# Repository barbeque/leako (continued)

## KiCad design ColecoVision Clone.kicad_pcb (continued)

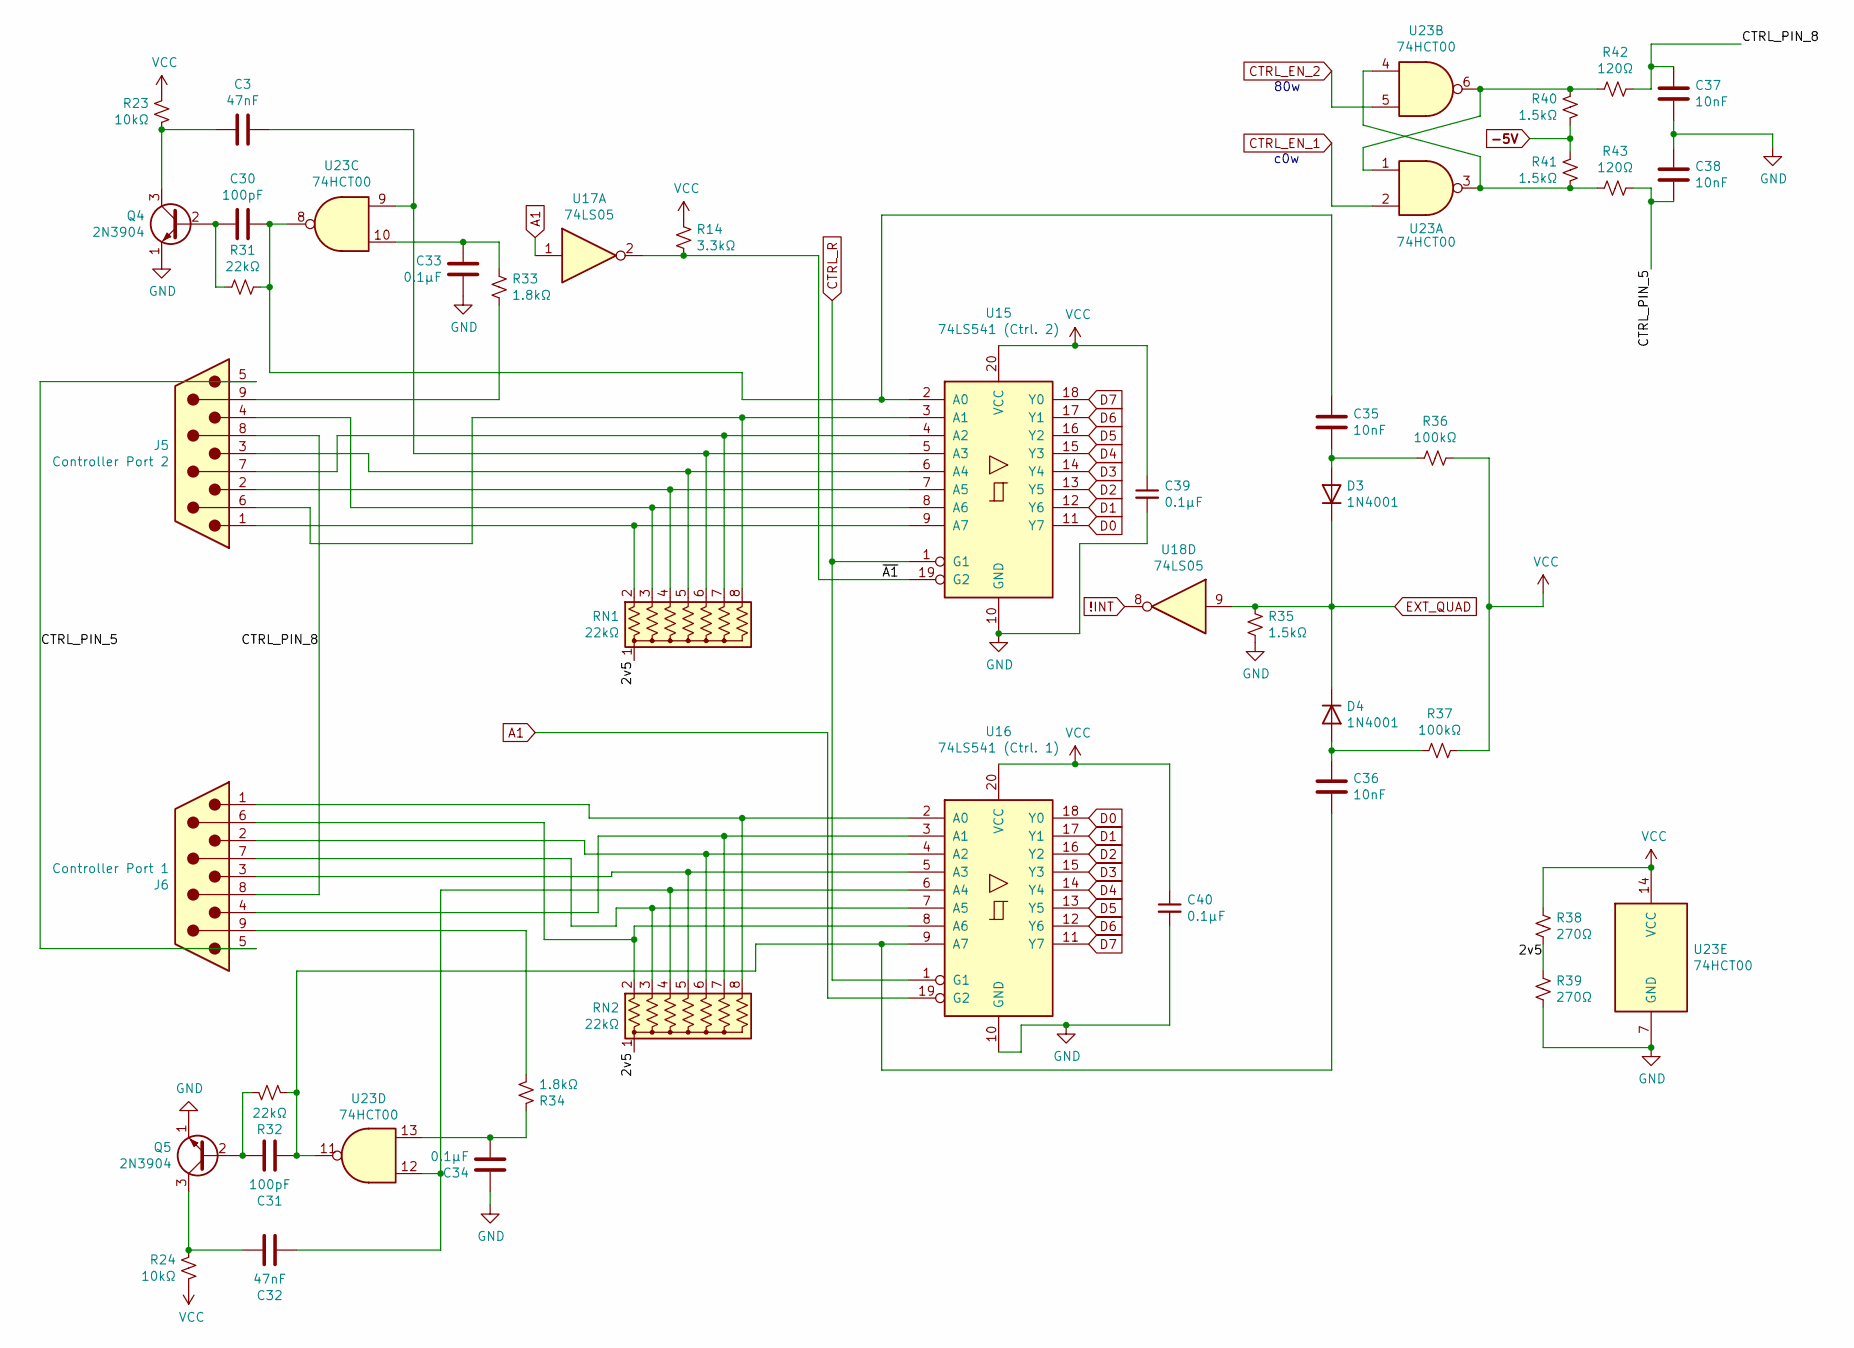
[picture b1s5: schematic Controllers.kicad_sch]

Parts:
C3, C32: 47nF; C_0805_HandSoldering; DigiKey 732-8059-1-ND
C30, C31: 100pF; C_0805_HandSoldering; DigiKey 732-12161-1-ND
C33, C34: 0.1µF; C_0805_HandSoldering; DigiKey 1276-1099-1-ND
C35, C36, C37, C38: 10nF; C_0805_HandSoldering; DigiKey 399-C0805X103K1RAC3316CT-ND
C39, C40: 0.1µF; C_0805_2012Metric_Pad1.15x1.40mm_HandSolder; DigiKey 1276-1099-1-ND
D3, D4: 1N4001; D_DO-41_SOD81_P2.54mm_Vertical_AnodeUp; DigiKey 641-1310-1-ND
J5: Controller Port 2; A-DS 09 A-KG-T2S; DigiKey AE10968-ND
J6: Controller Port 1; A-DS 09 A-KG-T2S; DigiKey AE10968-ND
Q4, Q5: 2N3904; TO-92_Inline_Wide; DigiKey 2N3904TAFSCT-ND
R14: 3.3kΩ; R_0805_HandSoldering; DigiKey RMCF0805JT3K30CT-ND
R23, R24: 10kΩ; R_0805_HandSoldering; DigiKey RMCF0805JT10K0CT-ND
R31, R32: 22kΩ; R_0805_HandSoldering; DigiKey RMCF0805JT22K0CT-ND
R33, R34: 1.8kΩ; R_0805_HandSoldering; DigiKey RMCF0805JT1K80CT-ND
R35, R40, R41: 1.5kΩ; R_0805_HandSoldering; DigiKey RMCF0805JT1K50CT-ND
R36, R37: 100kΩ; R_0805_HandSoldering; DigiKey RMCF0805JT100KCT-ND
R38, R39: 270Ω; R_0805_HandSoldering; DigiKey RMCF0805JT270RCT-ND
R42, R43: 120Ω; R_0805_HandSoldering; DigiKey RMCF0805JT120RCT-ND
RN1, RN2: 22kΩ; R_Array_SIP8; DigiKey 4608X-1-223LF-ND
U15: 74LS541 (Ctrl. 2); SOIC-20W_7.5x12.8mm_P1.27mm; DigiKey 296-14870-1-ND
U16: 74LS541 (Ctrl. 1); SOIC-20W_7.5x12.8mm_P1.27mm; DigiKey 296-14870-1-ND
U17, U18: 74LS05; SOIC-14_3.9x8.7mm_Pitch1.27mm; DigiKey 296-1630-1-ND
U23: 74HCT00; SOIC-14_3.9x8.7mm_Pitch1.27mm; DigiKey 296-14542-1-ND

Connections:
!INT: U18.8; also elsewhere on the board
-5V: R40.1, R41.2; also elsewhere on the board
/Controllers/2v5: R38.2, R39.1, RN1.1 (common), RN2.1 (common)
/Controllers/CTRL_PIN_5: C38.2, J5.5, J6.5, R43.1
/Controllers/CTRL_PIN_8: C37.1, J5.8, J6.8, R42.1
/Controllers/~A1: R14.2, U15.19 (G2), U17.2
A1: U16.19 (G2), U17.1; also elsewhere on the board
CTRL_EN_1: U23.2; also elsewhere on the board
CTRL_EN_2: U23.5; also elsewhere on the board
CTRL_R: U15.1 (G1), U16.1 (G1); also elsewhere on the board
D0: U15.11 (Y7), U16.18 (Y0); also elsewhere on the board
D1: U15.12 (Y6), U16.17 (Y1); also elsewhere on the board
D2: U15.13 (Y5), U16.16 (Y2); also elsewhere on the board
D3: U15.14 (Y4), U16.15 (Y3); also elsewhere on the board
D4: U15.15 (Y3), U16.14 (Y4); also elsewhere on the board
D5: U15.16 (Y2), U16.13 (Y5); also elsewhere on the board
D6: U15.17 (Y1), U16.12 (Y6); also elsewhere on the board
D7: U15.18 (Y0), U16.11 (Y7); also elsewhere on the board
EXT_QUAD: D3.1 (K), D4.1 (K), R35.2, U18.9; also elsewhere on the board
GND: C33.1, C34.2, C37.2, C38.1, C39.2, C40.2, Q4.1 (E), Q5.1 (E), R35.1, R39.2, U15.10 (GND), U16.10 (GND), U23.7 (GND); also elsewhere on the board
unnamed: C3.1, RN1.6 (R5), U15.5 (A3), U23.9
unnamed: C3.2, Q4.3 (C), R23.1
unnamed: C30.1, C35.1, R31.1, U15.2 (A0), U23.8
unnamed: C30.2, Q4.2 (B), R31.2
unnamed: C31.1, C36.2, R32.1, U16.9 (A7), U23.11
unnamed: C31.2, Q5.2 (B), R32.2
unnamed: C32.1, RN2.4 (R3), U16.6 (A4), U23.12
unnamed: C32.2, Q5.3 (C), R24.2
unnamed: C33.2, R33.2, U23.10
unnamed: C34.1, R34.2, U23.13
unnamed: C35.2, D3.2 (A), R36.2
unnamed: C36.1, D4.2 (A), R37.2
unnamed: J5.1, RN1.2 (R1), U15.9 (A7)
unnamed: J5.2, RN1.4 (R3), U15.7 (A5)
unnamed: J5.3, RN1.5 (R4), U15.6 (A4)
unnamed: J5.4, RN1.3 (R2), U15.8 (A6)
unnamed: J5.6, RN1.8 (R7), U15.3 (A1)
unnamed: J5.7, RN1.7 (R6), U15.4 (A2)
unnamed: J5.9, R33.1
unnamed: J6.1, RN2.8 (R7), U16.2 (A0)
unnamed: J6.2, RN2.6 (R5), U16.4 (A2)
unnamed: J6.3, RN2.5 (R4), U16.5 (A3)
unnamed: J6.4, RN2.7 (R6), U16.3 (A1)
unnamed: J6.6, RN2.2 (R1), U16.8 (A6)
unnamed: J6.7, RN2.3 (R2), U16.7 (A5)
unnamed: J6.9, R34.1
unnamed: R40.2, R42.2, U23.1, U23.6
unnamed: R41.1, R43.2, U23.3, U23.4
VCC: C39.1, C40.1, R14.1, R23.2, R24.1, R36.1, R37.1, R38.1, U15.20 (VCC), U16.20 (VCC), U23.14 (VCC); also elsewhere on the board

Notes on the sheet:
c0w
80w

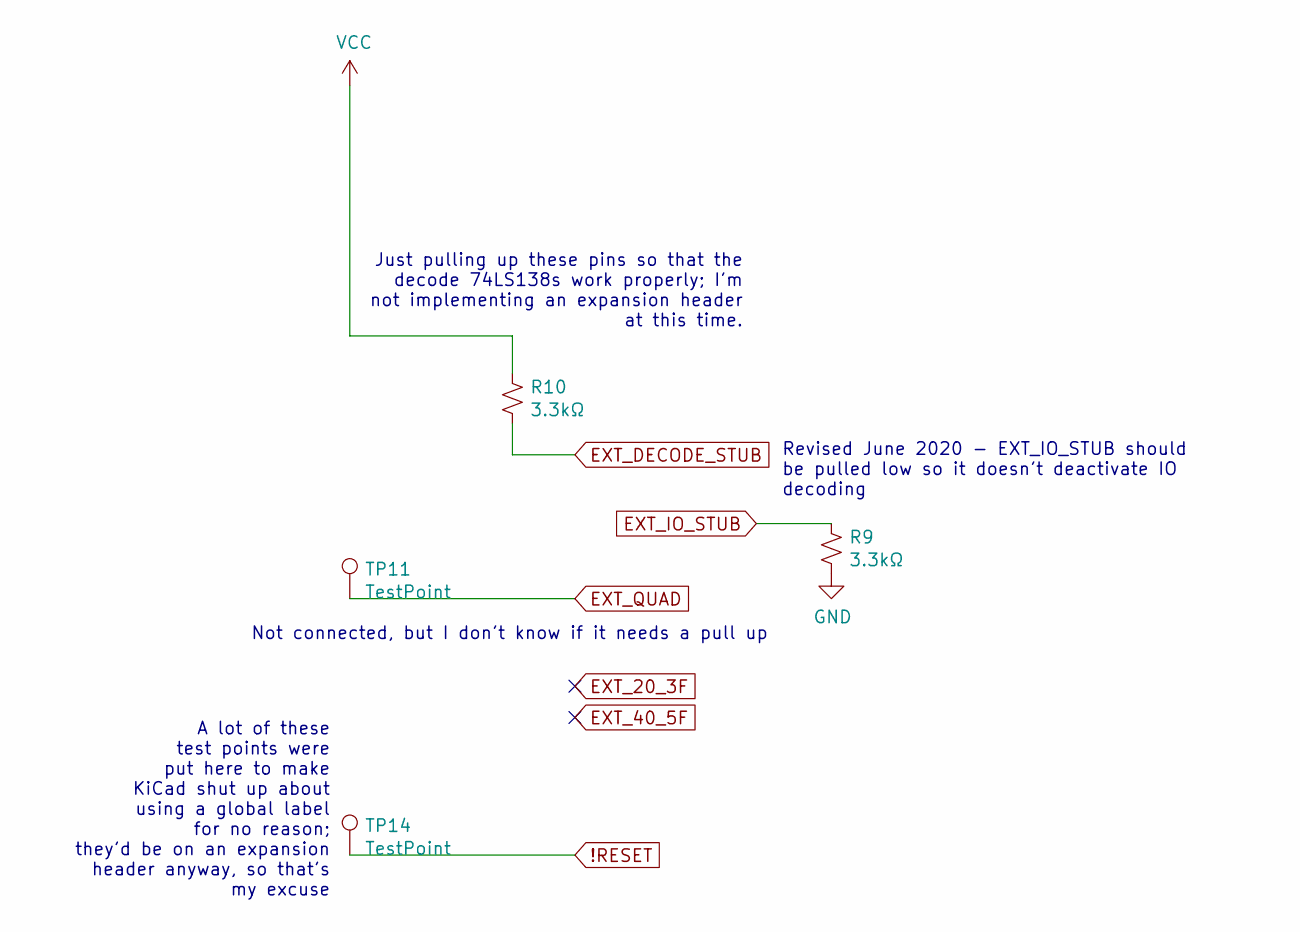
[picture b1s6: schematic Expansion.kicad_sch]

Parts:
R9, R10: 3.3kΩ; R_0805_HandSoldering; DigiKey RMCF0805JT3K30CT-ND
TP11: TestPoint; Measurement_Point_Round-TH_Small
TP14: TestPoint; Measurement_Point_Round-SMD-Pad_Small

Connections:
!RESET: TP14.1; also elsewhere on the board
EXT_DECODE_STUB: R10.2; also elsewhere on the board
EXT_IO_STUB: R9.2; also elsewhere on the board
EXT_QUAD: TP11.1; also elsewhere on the board
GND: R9.1; also elsewhere on the board
VCC: R10.1; also elsewhere on the board

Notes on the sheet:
Just pulling up these pins so that the decode 74LS138s work properly; I'm not implementing an expansion header at this time.
A lot of these test points were put here to make KiCad shut up about using a global label for no reason; they'd be on an expansion header anyway, so that's my excuse
Revised June 2020 - EXT_IO_STUB should be pulled low so it doesn't deactivate IO decoding
Not connected, but I don't know if it needs a pull up

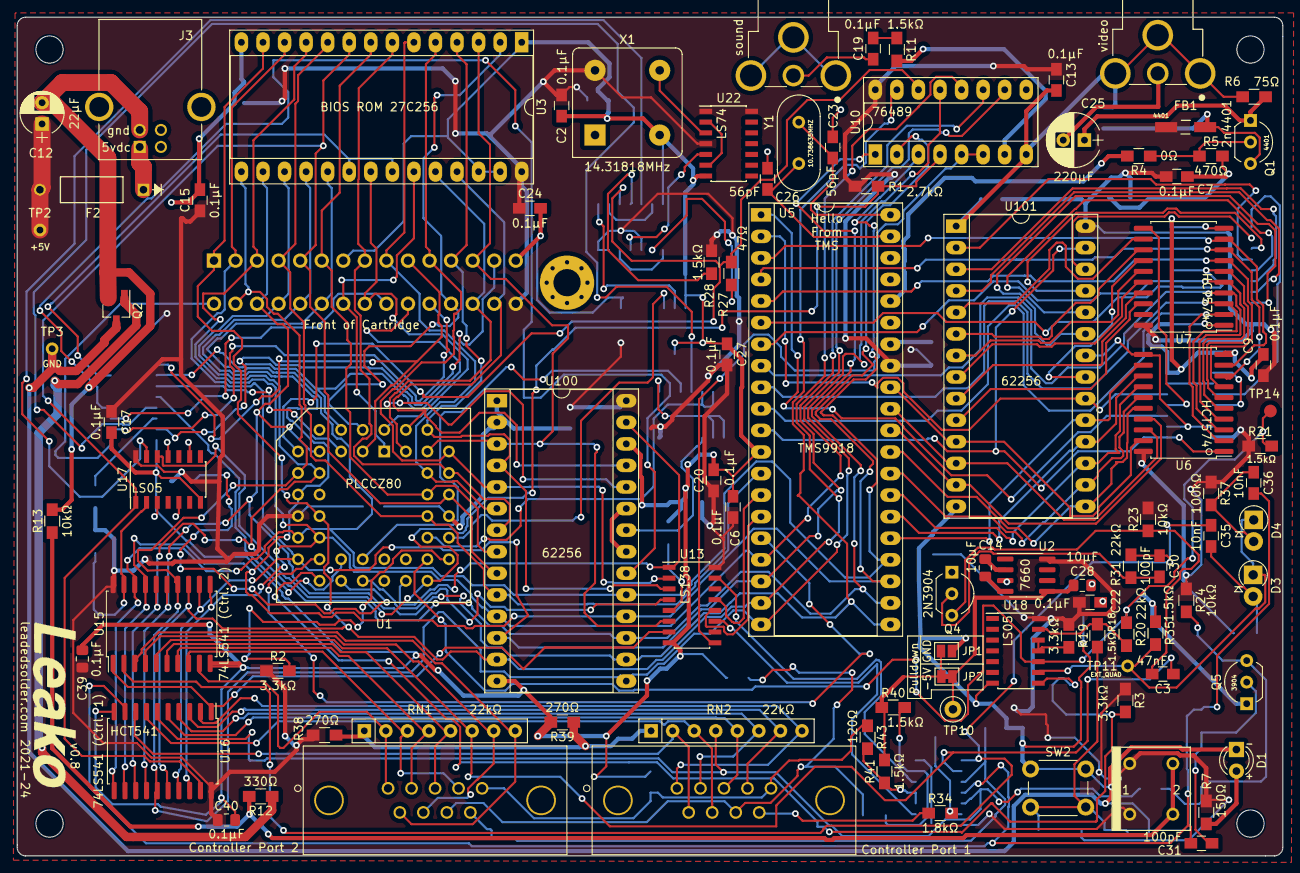
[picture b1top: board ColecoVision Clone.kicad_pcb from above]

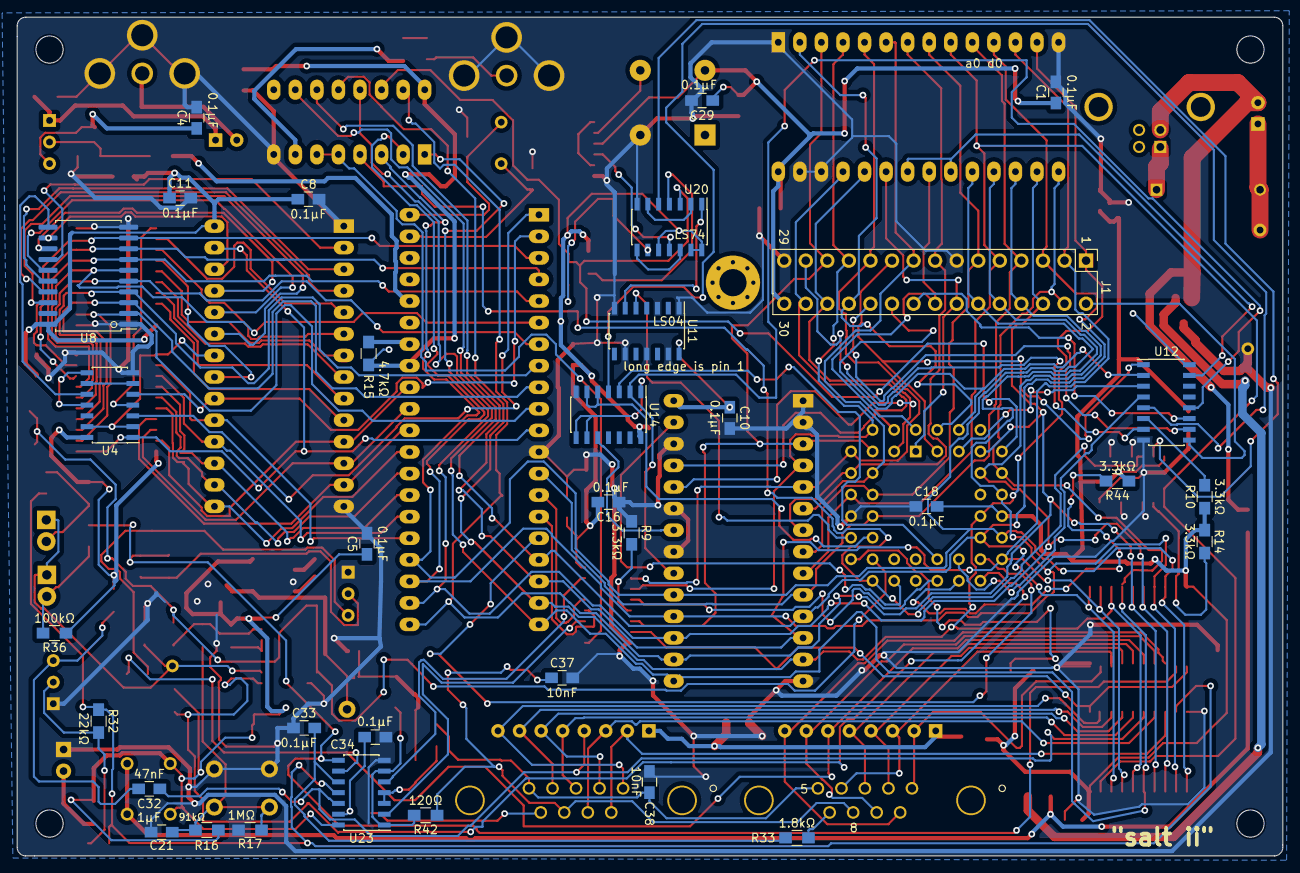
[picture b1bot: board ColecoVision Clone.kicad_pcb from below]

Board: 2 copper layers, 149.1 x 98.8 mm, 128 parts (34 on the bottom side), 159 nets.

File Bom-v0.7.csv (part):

"Customer Reference","Component Name","Value","Footprint","Part Number","Quantity","Description"
"C1, C2, C4, C5, C6, C7, C8, C9, C10, C11, C13, C15, C16, C17, C18, C19, C20, C22, C24, C27, C29, C33, C34","C","0.1µF","Capacitors_SMD:C_0805_HandSoldering","1276-1099-1-ND","23","Unpolarized capacitor"
"C3, C32","C","47nF","Capacitors_SMD:C_0805_HandSoldering","732-8059-1-ND","2","Unpolarized capacitor"
"C12","CP","22µF","Capacitors_ThroughHole:CP_Radial_D5.0mm_P2.50mm","493-1037-ND","1","Polarized capacitor"
"C14, C28","C_Small","10µF","Capacitor_SMD:C_0805_2012Metric_Pad1.15x1.40mm_HandSolder","1276-1298-1-ND","2","Unpolarized capacitor, small symbol"
"C21","C","1µF","Capacitors_SMD:C_0805_HandSoldering","1276-2926-1-ND","1","Unpolarized capacitor"
"C23, C26","C_Small","56pF","Capacitors_SMD:C_0805_HandSoldering","732-7817-1-ND","2","Unpolarized capacitor, small symbol"
"C25","CP1_Small","220µF","Capacitors_ThroughHole:CP_Radial_D6.3mm_P2.50mm","493-15121-ND","1","Polarized capacitor, small US symbol"
"C30, C31","C","100pF","Capacitors_SMD:C_0805_HandSoldering","732-12161-1-ND","2","Unpolarized capacitor"
"C35, C36, C37, C38","C","10nF","Capacitors_SMD:C_0805_HandSoldering","399-C0805X103K1RAC3316CT-ND","4","Unpolarized capacitor"
"D1","LED","LED","LEDs:LED_D3.0mm","1497-1022-ND","1","Light emitting diode"
"D3, D4","1N4001","1N4001","Diodes_ThroughHole:D_DO-41_SOD81_P2.54mm_Vertical_AnodeUp","641-1310-1-ND","2","50V 1A General Purpose Rectifier Diode, DO-41"
"F2","Fuse_Small","2A","0251002.MRT1L:0251002.MRT1L","F3171CT-ND","1","Fuse, small symbol"
"FB1","Ferrite_Bead_Small","Bead","Choke_SMD:Choke_SMD_1206_Handsoldering","283-MFBW1V3216-310-RCT-ND","1","Ferrite bead, small symbol"
"J1","Conn_02x15_Odd_Even","Cartridge Slot","LeakyChips:Sullins_Cart_Slot","S3305-ND","1","Generic connector, double row, 02x15, odd/even pin numbering scheme (row 1 odd numbers, row 2 even numbers), script generated (kicad-library-utils/schlib/autogen/connector/)"
"J2","RCJ-017","Composite video","Jacks:CUI_RCJ-017","CP-1403-ND‎","1",""
"J3","USB-B1HSB6","USB-B1HSB6","OST_USB-B1HSB6","ED2982-ND","1",""
"J4","RCJ-017","RCJ-013","Jacks:CUI_RCJ-017","CP-1402-ND‎","1",""
"J5","DB9_Male","Controller Port 2","Jacks:A-DS 09 A-KG-T2S","AE10968-ND","1","9-pin male D-SUB connector"
"J6","DB9_Male","Controller Port 1","Jacks:A-DS 09 A-KG-T2S","AE10968-ND","1","9-pin male D-SUB connector"
"Q1","Q_NPN_EBC","2n4401","TO_SOT_Packages_THT:TO-92_Inline_Wide","2N4401TFCT-ND","1","NPN transistor, emitter/base/collector"
"Q2","Q_NJFET_GSD","Q_NJFET_GSD","TO_SOT_Packages_SMD:SOT-23_Handsoldering","DMN6075S-7DICT-ND","1","N-JFET transistor, gate/source/drain"
"Q4, Q5","2N3904","2N3904","TO_SOT_Packages_THT:TO-92_Inline_Wide","2N3904TAFSCT-ND","2","0.2A Ic, 40V Vce, Small Signal NPN Transistor, TO-92"
"R1","R_Small_US","2.7kΩ","Resistors_SMD:R_0805_HandSoldering","RMCF0805JT2K70CT-ND","1","Resistor, small US symbol"
"R2, R3, R9, R10, R14, R19, R44","R_Small_US","3.3kΩ","Resistors_SMD:R_0805_HandSoldering","RMCF0805JT3K30CT-ND","7","Resistor, small US symbol"
"R4","R_Small_US","0Ω","Resistors_SMD:R_0805_HandSoldering","RMCF0805ZT0R00CT-ND","1","Resistor, small US symbol"
"R5","R_Small_US","470Ω","Resistors_SMD:R_0805_HandSoldering","RMCF0805JT470RCT-ND","1","Resistor, small US symbol"
"R6","R_Small_US","75Ω","Resistors_SMD:R_0805_HandSoldering","RMCF0805JT75R0CT-ND","1","Resistor, small US symbol"
"R7","R_Small_US","150Ω","Resistors_SMD:R_0805_HandSoldering","RMCF0805JT150RCT-ND","1","Resistor, small US symbol"
"R11, R18, R21, R28","R_Small_US","1kΩ","Resistors_SMD:R_0805_HandSoldering","RMCF0805FT1K00CT-ND","4","Resistor, small US symbol"
"R12","R_Small_US","330Ω","Resistors_SMD:R_0805_HandSoldering","RMCF0805JT330RCT-ND","1","Resistor, small US symbol"
"R13, R23, R24","R_Small_US","10kΩ","Resistors_SMD:R_0805_HandSoldering","RMCF0805JT10K0CT-ND","3","Resistor, small US symbol"
"R15","R_Small_US","4.7kΩ","Resistors_SMD:R_0805_HandSoldering","RMCF0805JT4K70CT-ND","1","Resistor, small US symbol"
"R16","R_Small_US","91kΩ","Resistors_SMD:R_0805_HandSoldering","RMCF0805JT91K0CT-ND","1","Resistor, small US symbol"
"R17","R_Small_US","1MΩ","Resistors_SMD:R_0805_HandSoldering","RMCF0805JT1M00CT-ND","1","Resistor, small US symbol"
"R20, R31, R32","R_Small_US","22kΩ","Resistors_SMD:R_0805_HandSoldering","RMCF0805JT22K0CT-ND","3","Resistor, small US symbol"
"R27","R_Small_US","47Ω","Resistors_SMD:R_0805_HandSoldering","RMCF0805JT47R0CT-ND","1","Resistor, small US symbol"
"R33, R34","R_Small_US","1.8kΩ","Resistors_SMD:R_0805_HandSoldering","RMCF0805JT1K80CT-ND","2","Resistor, small US symbol"
"R35, R40, R41","R_Small_US","1.5kΩ","Resistors_SMD:R_0805_HandSoldering","RMCF0805JT1K50CT-ND","3","Resistor, small US symbol"
"R36, R37","R_Small_US","100kΩ","Resistors_SMD:R_0805_HandSoldering","RMCF0805JT100KCT-ND","2","Resistor, small US symbol"
"R38, R39","R_Small_US","270Ω","Resistors_SMD:R_0805_HandSoldering","RMCF0805JT270RCT-ND","2","Resistor, small US symbol"
"R42, R43","R_Small_US","120Ω","Resistors_SMD:R_0805_HandSoldering","RMCF0805JT120RCT-ND","2","Resistor, small US symbol"
"RN1, RN2","R_Network07_US","22kΩ","Resistors_ThroughHole:R_Array_SIP8","4608X-1-223LF-ND","2","7 resistor network, star topology, bussed resistors, small US symbol"
"SW1","SW_Push","Power Toggle","LeakyChips:PVA1_Switch","401-1132-ND","1","Push button switch, generic, two pins"
"SW2","SW_Push","Reset","Buttons_Switches_ThroughHole:SW_PUSH_6mm","679-2428-ND","1","Push button switch, generic, two pins"
"TP2, TP3, TP11","TestPoint","TestPoint","Measurement_Points:Measurement_Point_Round-TH_Small","","3","test point"
"TP10","TestPoint","-5V","Measurement_Points:Measurement_Point_Round-SMD-Pad_Small","","1","test point"
"TP14","TestPoint","TestPoint","Measurement_Points:Measurement_Point_Round-SMD-Pad_Small","","1","test point"
"U1","PLCCZ80","PLCCZ80","Sockets:PLCC44","2057-PLCC-44-AT-ND","1","The PLCC variant of the Zilog Z80"
"U1","PLCCZ80","PLCCZ80","Sockets:PLCC44"," 269-3899-ND","1","The PLCC variant of the Zilog Z80"
"U2","ICL7660","ICL7660","Package_SO:SOIC-8_3.9x4.9mm_P1.27mm","ICL7660CSA+TCT-ND","1","Switched-Capacitor Voltage Converter, 1.5V to 10.0V operating supply voltage, 10mA with a 0.5V output drop, SO-8/DIP-8/µMAX-8/TO-99"
"U3","27C256","BIOS ROM 27C256","Housings_DIP:DIP-28_W15.24mm_Socket_LongPads","2057-ICS-628-T-ND","1","OTP EPROM 256 KiBit"
"U4, U11","74LS04","74HCT04","Housings_SOIC:SOIC-14_3.9x8.7mm_Pitch1.27mm","296-31832-1-ND","2","Hex Inverter"
"U5","TMS9918A","TMS9918A","Housings_DIP:DIP-40_W15.24mm_Socket_LongPads","ED3048-5-ND","1",""
"U6, U7, U8","74LS574","74HCT574","Housings_SOIC:SOIC-20W_7.5x12.8mm_Pitch1.27mm","1727-2856-1-ND","3","8-bit Register, 3-state outputs"
"U10","SN76489AN","SN76489AN","Housings_DIP:DIP-16_W7.62mm_Socket_LongPads","AE9992-ND","1",""
"U12","74LS138","74LS138 (Mem. Mapped)","Housings_SOIC:SOIC-16_3.9x9.9mm_Pitch1.27mm","296-14883-2-ND","1","Decoder 3 to 8 active low outputs"
"U13","74LS138","74LS138 (I/O)","Housings_SOIC:SOIC-16_3.9x9.9mm_Pitch1.27mm","296-14883-2-ND","1","Decoder 3 to 8 active low outputs"
"U14","74LS02","74LS02","Housings_SOIC:SOIC-14_3.9x8.7mm_Pitch1.27mm","296-14874-1-ND","1","quad 2-input NOR gate"
"U15","74LS541","74LS541 (Ctrl. 2)","Package_SO:SOIC-20W_7.5x12.8mm_P1.27mm","296-14870-1-ND","1","8-bit Buffer/Line Driver 3-state outputs"
"U16","74LS541","74LS541 (Ctrl. 1)","Package_SO:SOIC-20W_7.5x12.8mm_P1.27mm","296-14870-1-ND","1","8-bit Buffer/Line Driver 3-state outputs"
"U17, U18","74LS05","74LS05","Housings_SOIC:SOIC-14_3.9x8.7mm_Pitch1.27mm","296-1630-1-ND","2","Inverter Open Collect"
"U20, U22","74LS74","74LS74","Housings_SOIC:SOIC-14_3.9x8.7mm_Pitch1.27mm","296-14899-1-ND","2","Dual D Flip-flop, Set & Reset"
"U23","74HCT00","74HCT00","Housings_SOIC:SOIC-14_3.9x8.7mm_Pitch1.27mm","296-14542-1-ND","1","quad 2-input NAND gate"
"U100, U101","AS6C62256-DIP","AS6C62256-DIP","Housings_DIP:DIP-28_W15.24mm_Socket_LongPads","1450-1033-ND","2",""
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
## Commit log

2020-02-03 Early PCB - just cart slot and CPU
2020-02-03 Cleaning up cache
2020-02-03 TODO
2020-02-03 Partially fucked up chip layout
2020-02-03 Not happy with label posn but it's workign
2020-02-03 SOIC-40 footprint, needs testing
2020-02-03 This is fun, and hard
2020-02-03 Leako logo
2020-02-03 More TODO
2020-02-03 More todos
2020-02-04 Added a bunch of shit we don't need to distract me from doing RAM decoding
2020-02-04 Update TODO
2020-02-04 Wire to bus
2020-02-04 Bus fuss
2020-02-04 Kinda wiring up D-pins
2020-02-04 Maybe bus
2020-02-04 Blindly hooking up vram bus
2020-02-05 Not sure I know enough to set up the VRAM bus yet
2020-02-05 Get rid of RD0 speculation
2020-02-05 DRAM todo
2020-02-05 Sram-Adapter
2020-02-05 Add PDF for SRAM replacement
2020-02-05 Wish list items
2020-02-05 More wishlist
2020-02-05 ADAM notes
2020-02-05 Port decode logic
2020-02-05 TMS addressing
2020-02-05 Cart decode
2020-02-06 COMVID and Crystal from PDF
2020-02-06 Rotate schematic page
2020-02-06 Entire VRAM decoder laid out
2020-02-06 updated TODO list
2020-02-06 Update pcb
2020-02-06 Disable first 1K
2020-02-06 little notes
2020-02-06 SN76489 part
2020-02-06 Audio jack no amp
2020-02-06 Re-introduce logo
2020-02-06 BIOS ROM
2020-02-06 Add the logo AGAIN
2020-02-06 Memory map decoder
2020-02-06 Fix decody
2020-02-06 Decody
2020-02-06 Disable upper pins
2020-02-06 work ram cap
2020-02-06 RAM, Cart, BIOS address pins
2020-02-06 Start plumbing out enable pins
2020-02-06 OE CE for RAM
2020-02-06 BIOS TODO
2020-02-06 Memory Decode
2020-02-06 BIOS CE mystery solved
2020-02-06 RAM finally write enabled
2020-02-06 Cleaning up some old labels
2020-02-06 Why even use buses
2020-02-07 Clean up power flags
2020-02-07 More wiring
2020-02-07 -5V question
2020-02-07 ColecoVision controller schematic
2020-02-08 Pull-up on expansion header
2020-02-08 Keep-out
2020-02-08 LM386 audio amp
2020-02-08 MAXIMUM GAIN
2020-02-08 Get rid of amp
2020-02-08 Better power switch found
2020-02-08 Fuse, partial psu..
2020-02-08 Swap tip and ring for composite, finish up power
2020-02-08 Controller ports
2020-02-09 More messing with controllers
2020-02-09 Lock screw holes
2020-02-09 Routing tips
2020-02-09 Add test point bodges
2020-02-09 Reset circuit
2020-02-09 Do not allow CPU to reset VDP
2020-02-09 Do some pruning
2020-02-09 Clock crystal bullshit
2020-02-09 2x clock
2020-02-09 Clock divider moved
2020-02-09 you know what
2020-02-09 CPU clock detached from VDP
2020-02-09 [PCB] CPU clock detached from VDP
2020-02-10 notes for later
2020-02-10 Soon the clock nightmare will be over
2020-02-10 Solder bridge jumpers
2020-02-10 SMD jumpers
2020-02-11 Notes
2020-02-11 Shunt to ground
2020-02-11 Ditch the polyfuse
2020-02-11 Jesus
2020-02-11 TODO for later
2020-02-11 All the controller stuff is on the PCB now
2020-02-11 TODO update
2020-02-11 -5V line added
2020-02-11 -5V updated
2020-02-11 Add test point
2020-02-11 Placing parts
2020-02-11 Put power and ground pins on more logic
2020-02-11 Knocking out bugs
2020-02-11 Bugs patched
2020-02-11 CPU-cart-BIOS
2020-02-11 RAM wired up but i don't like it
2020-02-12 More chips
2020-02-12 that's enough for one night
2020-02-12 Slowly stitching up the TMS
2020-02-12 Cart Enable wired up
2020-02-12 A14 decode
2020-02-13 BIOS jumpers
2020-02-13 Sound chip plugged into data bus
2020-02-13 A13 on decoder
2020-02-13 Getting ugly
2020-02-13 Goodbye to one inverter
2020-02-13 RFSH routed
2020-02-13 more resistors
2020-02-13 More controller action
2020-02-13 RESET
2020-02-13 I think just decoupling caps now
2020-02-13 the L is in
2020-02-13 stubs removed
2020-02-13 /BUSRQ
2020-02-13 CPU VCC
2020-02-13 powering chips
2020-02-13 HALT pullup
2020-02-13 Goodbye A15 testpoint
2020-02-13 Controller port passives
2020-02-13 Reset passives
2020-02-13 Special U24 cap
2020-02-13 Silence DRC
2020-02-13 Bits and bobs - ready for decouplers
2020-02-13 TMS passive
2020-02-13 U4 passive
2020-02-13 More decouplers
2020-02-13 more labels
2020-02-14 BIOS ROM decouple
2020-02-14 SO CLOSE
2020-02-14 All decouplers installed
2020-02-14 it's all in there baby
2020-02-14 Power and Ground planes added
2020-02-14 gitignore
2020-02-15 TODO for version 2
2020-02-16 v2 wishlist
2020-02-16 BOM from Digi-Key
2020-02-19 Change the 68uF in clock
2020-02-19 Oops
2020-02-19 reverse data bus for 76489
2020-02-19 Moving labels around
2020-02-20 Change 68uF to a non-polarized 1206
2020-02-20 capacitor indecision 2020
2020-02-22 Big pulldown
2020-02-24 Fix notes
2020-02-24 Fix clock circuit - v0.2
2020-02-24 Some change
2020-02-24 more cleanup
2020-02-27 Revision
2020-02-27 Move Q3 out of the way of the cartridge
2020-02-29 Drop a 74ls05 and use a NOR gate instead
2020-02-29 Stray track cleanup
2020-02-29 Redo floods
2020-02-29 BOM management
2020-03-06 More DigiKey fields
2020-03-06 Some more chips
2020-03-09 Move Work RAM down
2020-03-09 Makin notes
2020-03-10 Power jack moved inward
2020-03-14 Prototype Sullins cart slot
2020-03-14 new cart slot, hope clearance is good
2020-03-14 Get rid of cartridge slot silkscreen since it is probably wrong
2020-03-14 Move the confusing decoupling cap away from the crystal holes
2020-03-14 Clean up tracks
2020-03-19 Mad at myself
2020-03-20 Fuckin' oops
2020-03-20 Double oops
2020-03-24 v0.2 BOM
2020-03-25 Cleaning up v0.3 with some of the assembly findings
2020-03-25 Clean up units
2020-03-25 Unit fix again
2020-03-25 Wide TO-92s for the controller 2n3904s
2020-03-25 Move the C38 label
2020-03-25 Move one more around
2020-03-26 Move RAMs to J-lead package
2020-03-26 Move the circuit into the right spot of the page
2020-03-26 Even wider pads
2020-03-26 Add DigiKey callout for the 47ohm
2020-03-26 Taking notes
2020-03-26 Clean up some traces
2020-03-26 Publish v0.3 BOM
2020-03-27 It's mad time
2020-03-27 Squashed commit of the following:
    commit 0573e733ffc2a0f8f9404fb672cdf472d7d182e4
    Author: mike stedman <barbeque@users.noreply.github.com>
    Date: Fri Mar 27 07:56:41 2020 -0600
    Eat shit other me
    commit 68b1ea6bce640c772a96e1186761b76c8d888606
    Author: mike stedman <barbeque@users.noreply.github.com>
2020-03-29 Ignore BOM intermediate files
2020-03-31 Re-wire main power FET
2020-03-31 Beef up power rail
2020-04-01 Re-attach ground
2020-04-01 Fix some global label warnings
2020-04-01 PLCC Z80 bodge
2020-04-01 PLCC Z80 footprint - set inputs/outputs properly
2020-04-01 Fix /RFSH
2020-04-01 Better GND return line from LED
2020-04-01 LED polarity symbol
2020-04-01 Cleaning up more grounds
2020-04-01 Pull-ups on WRAM and VRAM upper byte
2020-04-01 Numbering
2020-04-01 Move unrelated chip away
2020-04-01 Cleaning up net names for debugging
2020-04-01 Remapped VRAM SRAM according to https://www.leonardomiliani.com/en/2019/lm80c-tms9918a/
2020-04-01 Attach U11 to power, add dedicated crystal for TMS
2020-04-01 U17 now powered
2020-04-01 Add DigiKey part number for 33pF clock caps
2020-04-02 Ground Vpp on the ROM
2020-04-03 Slowly clearing up vias
2020-04-03 Purging vias
2020-04-03 Many fewer vias in the sound chip
2020-04-03 Under 500 vias now
2020-04-03 A tough-won via removal
2020-04-03 Cleaning up power via
2020-04-03 v0.5 prototype, but not yet
2020-04-03 v0.5 BOM
2020-04-15 Update LS05 to 296-1630-1-ND
2020-06-09 Add 14mhz, 7mhz labels to nets
2020-06-09 Add test points, fix a gnarly trace
2020-06-09 Trace clean-up
2020-06-09 ECOs added
2020-06-10 Fix TMS9918 clock circuit
2020-06-10 56pF crystal caps
2020-06-12 Improve routing for VDC_R, VDC_W
2020-06-12 Get rid of EXT_QUAD and clean up the reset line
2020-06-12 Ditch one via on EXT_QUAD
2020-06-14 TODOs to fix the latest idiocy
2020-06-15 Apply all the bodges so far
2020-06-15 Use '05 for the /WAIT inversion, not an '04 which would conflict with the sound chip
2020-06-15 Hello World ported to the CV
2020-06-15 Output transistor fix
2020-06-16 Add 220uF output cap
2020-06-16 /WRAM_REFRESH circuit
2020-06-16 Route the new /WRAM_REFRESH circuit
2020-06-17 Change note to mention cap
2020-06-17 Get rid of a via
2020-06-18 Update symbols to use ~
2020-06-18 Add local copy of SRAM mod page
2020-06-18 Tie VRAM A14 to ground
2020-06-18 Fix the callouts for the SRAM logic
2020-06-23 Clean up stray trace
2020-06-24 Miliani link
2020-06-24 DIP-28 AS6C62256
2020-06-24 Main RAM swapped
2020-06-24 Replace VRAM with 62256
2020-06-24 Cap footprints
2020-06-24 RAM's down
2020-06-24 62256 through-hole VRAM
2020-06-24 62256 for VRAM and RAM
2020-06-24 Add data sheet for 62256 SRAM
2020-06-24 Change board tag
2020-07-02 v0.6 BOM PDF
2020-07-03 Fix silkscreen positions
2021-02-16 Starting to prepare for publication
2021-02-16 Fix the footnote
2021-02-16 Reliability
2021-02-16 Barrel jack reliability
2021-08-31 Make decody better
2021-09-22 Fix missing junction and bump version to 0.7
2021-10-07 Polarity mark
2021-10-26 Reorganize for easier reading
2021-10-26 Base to rewire quadrature
2021-10-26 Base before quadrature messing
2021-10-26 Flip controller port #s
2021-10-26 Use different 74541 symbol
2021-10-26 Thicken up some power traces
2021-10-26 Remove stray vcc pin
2021-10-26 Make the ground switching flipflop look better
2021-10-26 Getting a plan to merge unused logic
2021-10-26 Clean up sketchy pad
2021-11-02 Prepare for official release
2021-11-02 License on README
2021-11-02 Move some of the documents into another folder
2021-11-02 Header fix
2021-11-04 Accidentally moved library away, breaking schematic
2021-11-04 ICL7660 -5V reg
2021-11-04 ICL7220 on board
2021-11-04 Reinforcement hole near cartridge slot
2021-11-05 Using an obsolete DE9 may be dumb
2022-01-03 USB-B jack for power
2022-01-03 Better label passive values
2022-01-03 Change jacks for board (not routed yet)
2022-01-03 Squashed commit of the following:
    commit 92abf32cadf827114d19584acd122949932597b3
    Author: mike <barbeque@users.noreply.github.com>
    Date: Mon Jan 3 10:32:57 2022 -0700
    Routing complete for new controller port part
    commit b2f35945ec75921dc30cd07b50809f4682bd367a
    Author: mike <barbeque@users.noreply.github.com>
2022-01-03 U17 unused inputs grounded
2022-01-03 Ground unused inputs of u11
2022-01-03 General cleanup
2022-01-03 Nice radius on the board edges
2022-01-06 Address bits helper in decody
2022-01-07 Output format change
2022-01-17 v0.7 release notes
2022-02-03 Coloured RCA jacks
2022-02-15 BOM update
2022-02-17 DigiKey BOM complete
2022-02-17 Label the big chips too
2022-02-18 CSV BOM exporter
2022-02-18 Change to more available power FET
2022-02-23 Per-project prefix on CSV BOM
2022-03-09 Bypass caps for 541s
2022-03-09 Slightly better silks
2022-03-10 Replace 1k with 1.5k across the board to reduce BOM
2022-03-10 Move pads around de9
2022-03-18 Mounting hole moved
2022-03-19 Wider lands on the '574s
2022-03-24 Clean up old notes
2022-04-06 Move C25 away from video port so it doesn't hit the connector
2022-04-06 Send chips to other side so they don't interfere with cart slot
2022-04-06 Moved some passives away from the edge
2022-04-06 Move some labels
2022-04-17 v0.8 in-progress change notes
2022-04-20 Use TE AMP 5530843-2 cartridge slot, same as v0.6
2022-05-10 Finally added bodge jumper to defeat ICL7660 and pull down to ground
2022-05-11 Use a consistent test point for -5v
2022-05-11 Add ground pads to controller connectors
2022-05-12 label pins 5, 8 on controls
2022-09-18 Convert pcb, schematic, project to KiCad6
2022-09-19 Clearance problems, pours fixed
2022-09-19 Get rid of old Testpoints schematic
2022-09-19 Upgrade to KiCad 6
2022-09-19 KiCad 6 readme
2023-01-24 System C-2 decoder map, 32-bit extension mode
2023-11-27 Releases link
2024-04-19 Use solid connections for pours instead of spokes
2024-04-19 Bump date
2024-04-19 Link to DigiKey BOM List
2024-05-14 Ignore ibom output
2024-05-14 Link to releases page
2024-05-27 PC-6001 I/O map
2024-08-30 ADAM I/O map
2024-09-25 Laser-cut case files from Cheshire Noir
2024-11-01 Known issue: power-on
2025-02-26 Working sound test cartridge, non-BIOS
2025-02-26 Attempting to make a dead test bios that makes soiund
2025-02-26 Partially successful sound test
2025-12-23 Update to KiCad 9
2025-12-23 Include PDF schematics
2025-12-23 Rename
